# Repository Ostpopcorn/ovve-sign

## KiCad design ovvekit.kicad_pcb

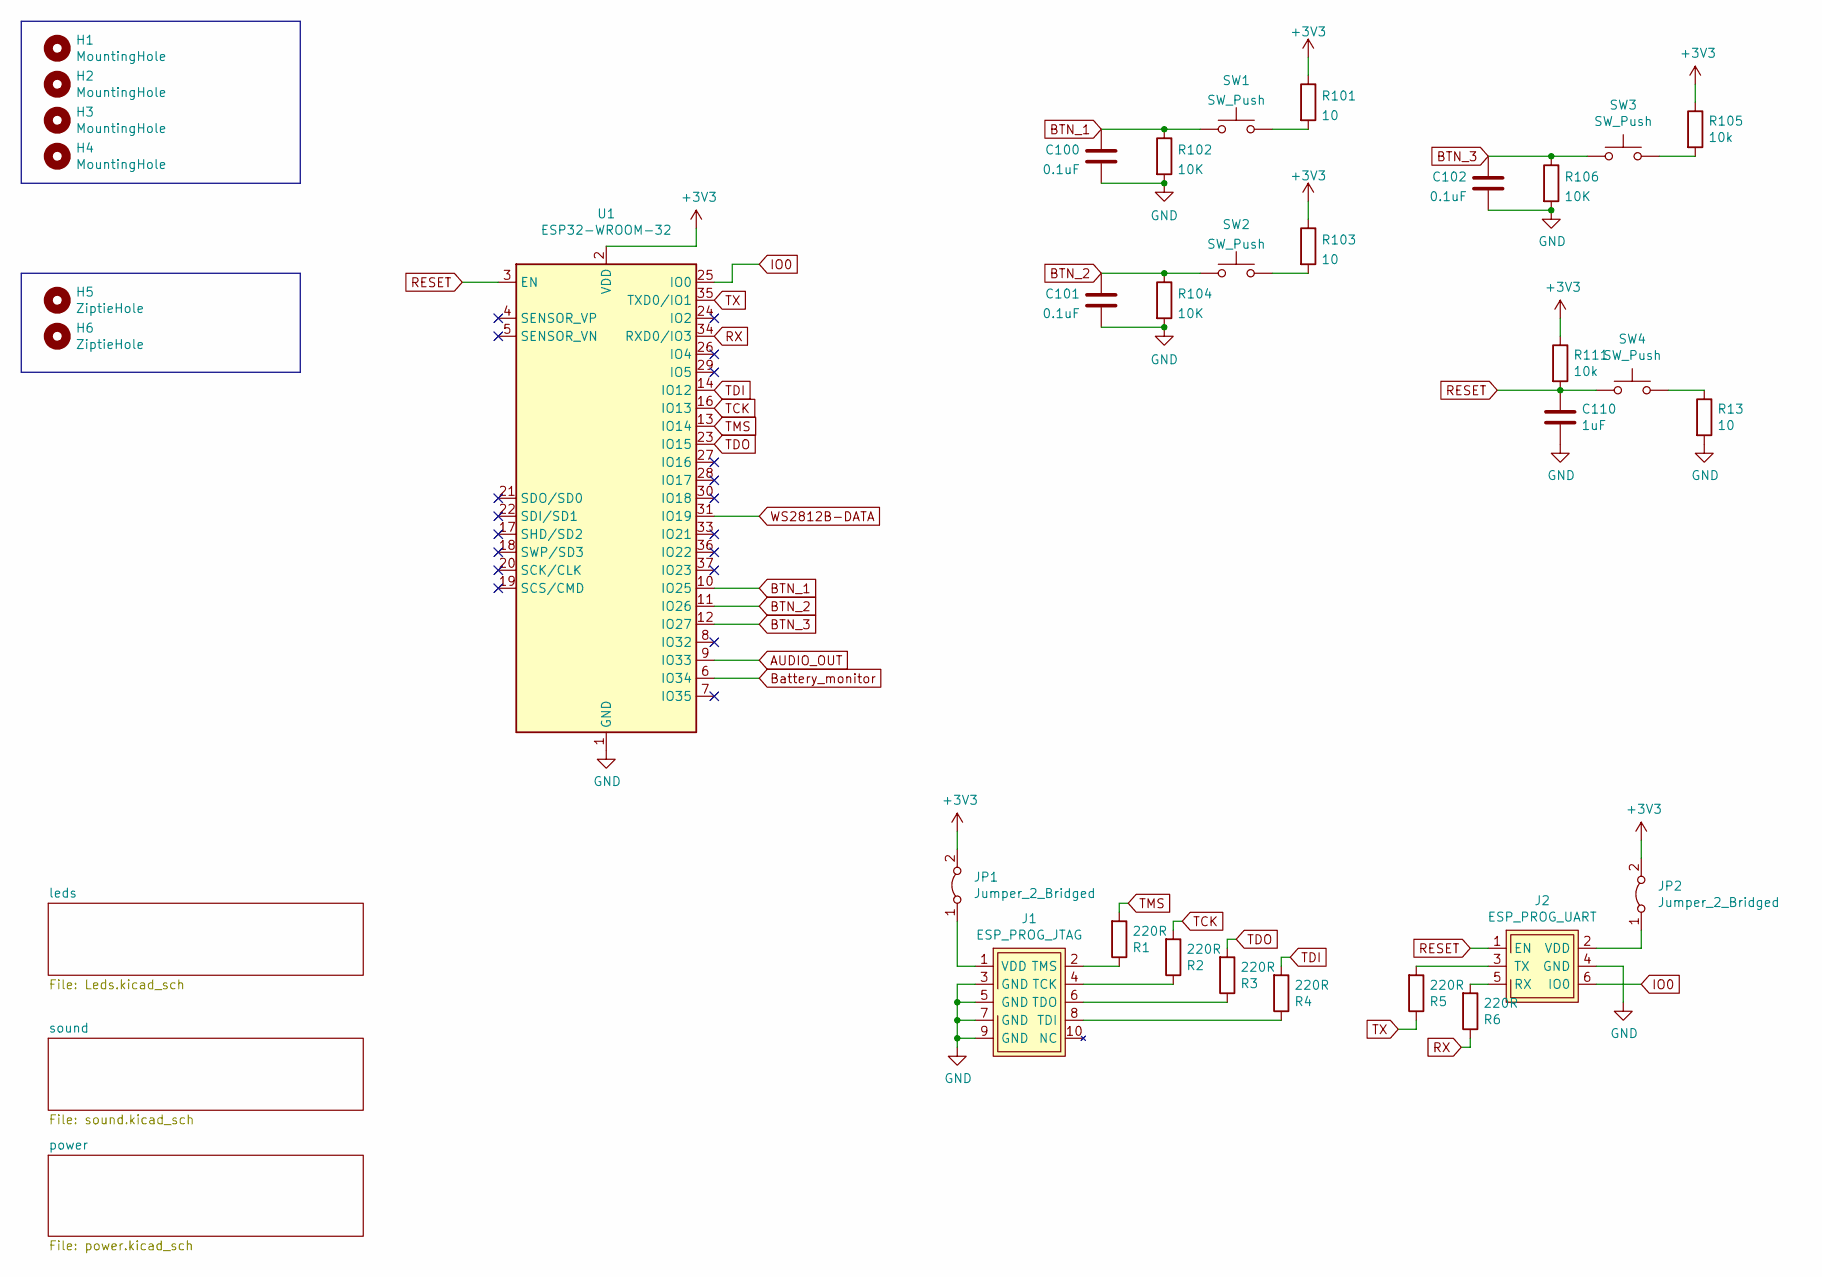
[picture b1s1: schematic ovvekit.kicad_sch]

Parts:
C100, C101, C102: 0.1uF; C_0603_1608Metric_Pad1.08x0.95mm_HandSolder
C110: 1uF; C_0603_1608Metric_Pad1.08x0.95mm_HandSolder
H1, H2, H3, H4: MountingHole; MountingHole_3.2mm_M3_ISO7380
H5, H6: ZiptieHole; MountingHole_2.7mm_M2.5_ISO7380
J1: ESP_PROG_JTAG; SMT_ESP_PROG_JTAG_1.27
J2: ESP_PROG_UART; SMT_ESP_PROG_PROG_1.27
JP1, JP2: Jumper_2_Bridged; SolderJumper-2_P1.3mm_Open_TrianglePad1.0x1.5mm
R1, R2, R3, R4, R5, R6: 220R; R_0603_1608Metric_Pad0.98x0.95mm_HandSolder
R13, R101, R103: 10; R_0603_1608Metric_Pad0.98x0.95mm_HandSolder
R102, R104, R106: 10K; R_0603_1608Metric_Pad0.98x0.95mm_HandSolder
R105, R111: 10k; R_0603_1608Metric_Pad0.98x0.95mm_HandSolder
SW1, SW2, SW3: SW_Push; SW_PUSH_6mm_H5mm
SW4: SW_Push; SW_SPST_TL3342
U1: ESP32-WROOM-32

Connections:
AUDIO_OUT: U1.9 (IO33); also elsewhere on the board
BTN_1: C100.1, R102.1, SW1.1, U1.10 (IO25)
BTN_2: C101.1, R104.1, SW2.1, U1.11 (IO26)
BTN_3: C102.1, R106.1, SW3.1, U1.12 (IO27)
Battery_monitor: U1.6 (IO34); also elsewhere on the board
GND: C100.2, C101.2, C102.2, C110.2, J1.3 (GND), J1.5 (GND), J1.7 (GND), J1.9 (GND), J2.4 (GND), R13.2, R102.2, R104.2, R106.2, U1.1 (GND), U1.15 (GND), U1.38 (GND), U1.39 (GND); also elsewhere on the board
IO0: J2.6 (IO0), U1.25 (IO0)
unnamed: J1.1 (VDD), JP1.1 (A)
unnamed: J1.2 (TMS), R1.1
unnamed: J1.4 (TCK), R2.1
unnamed: J1.6 (TDO), R3.1
unnamed: J1.8 (TDI), R4.1
unnamed: J2.2 (VDD), JP2.1 (A)
unnamed: J2.3 (TX), R5.2
unnamed: J2.5 (RX), R6.2
unnamed: R101.2, SW1.2
unnamed: R103.2, SW2.2
unnamed: R105.2, SW3.2
unnamed: R13.1, SW4.2
RESET: C110.1, J2.1 (EN), R111.2, SW4.1, U1.3 (EN)
RX: R6.1, U1.34 (RXD0/IO3)
TCK: R2.2, U1.16 (IO13)
TDI: R4.2, U1.14 (IO12)
TDO: R3.2, U1.23 (IO15)
TMS: R1.2, U1.13 (IO14)
TX: R5.1, U1.35 (TXD0/IO1)
WS2812B-DATA: U1.31 (IO19); also elsewhere on the board

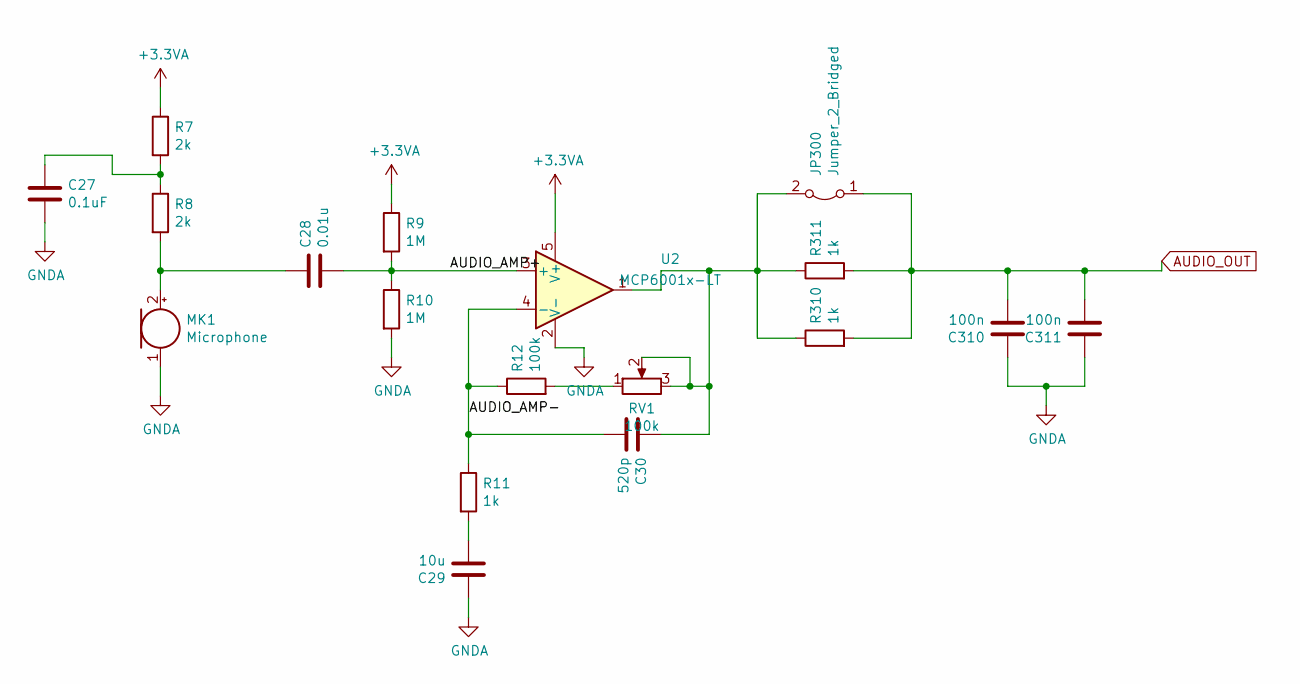
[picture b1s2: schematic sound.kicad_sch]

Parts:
C27: 0.1uF; C_0603_1608Metric_Pad1.08x0.95mm_HandSolder
C28: 0.01u; C_0603_1608Metric_Pad1.08x0.95mm_HandSolder
C29: 10u; C_0603_1608Metric_Pad1.08x0.95mm_HandSolder
C30: 520p; C_0603_1608Metric_Pad1.08x0.95mm_HandSolder
C310, C311: 100n; C_0603_1608Metric_Pad1.08x0.95mm_HandSolder
JP300: Jumper_2_Bridged; SolderJumper-2_P1.3mm_Open_TrianglePad1.0x1.5mm
MK1: Microphone; CMEJ062742P
R7, R8: 2k; R_0603_1608Metric_Pad0.98x0.95mm_HandSolder
R9, R10: 1M; R_0603_1608Metric_Pad0.98x0.95mm_HandSolder
R11, R310, R311: 1k; R_0603_1608Metric_Pad0.98x0.95mm_HandSolder
R12: 100k; R_0603_1608Metric_Pad0.98x0.95mm_HandSolder
RV1: 100k; Potentiometer_Bourns_3314S_Horizontal
U2: MCP6001x-LT; SOT-23-5

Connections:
+3.3VA: R7.1, R9.1, U2.5 (V+); also elsewhere on the board
/sound/AUDIO_AMP+: C28.2, R9.2, R10.1, U2.3 (+)
/sound/AUDIO_AMP-: C30.2, R11.1, R12.1, U2.4 (-)
AUDIO_OUT: C310.2, C311.2, JP300.1 (A), R310.2, R311.2; also elsewhere on the board
GNDA: C27.2, C29.1, C310.1, C311.1, MK1.1 (-), R10.2, U2.2 (V-); also elsewhere on the board
unnamed: C27.1, R7.2, R8.1
unnamed: C28.1, MK1.2 (+), R8.2
unnamed: C29.2, R11.2
unnamed: C30.1, JP300.2 (B), R310.1, R311.1, RV1.2, RV1.3, U2.1
unnamed: R12.2, RV1.1

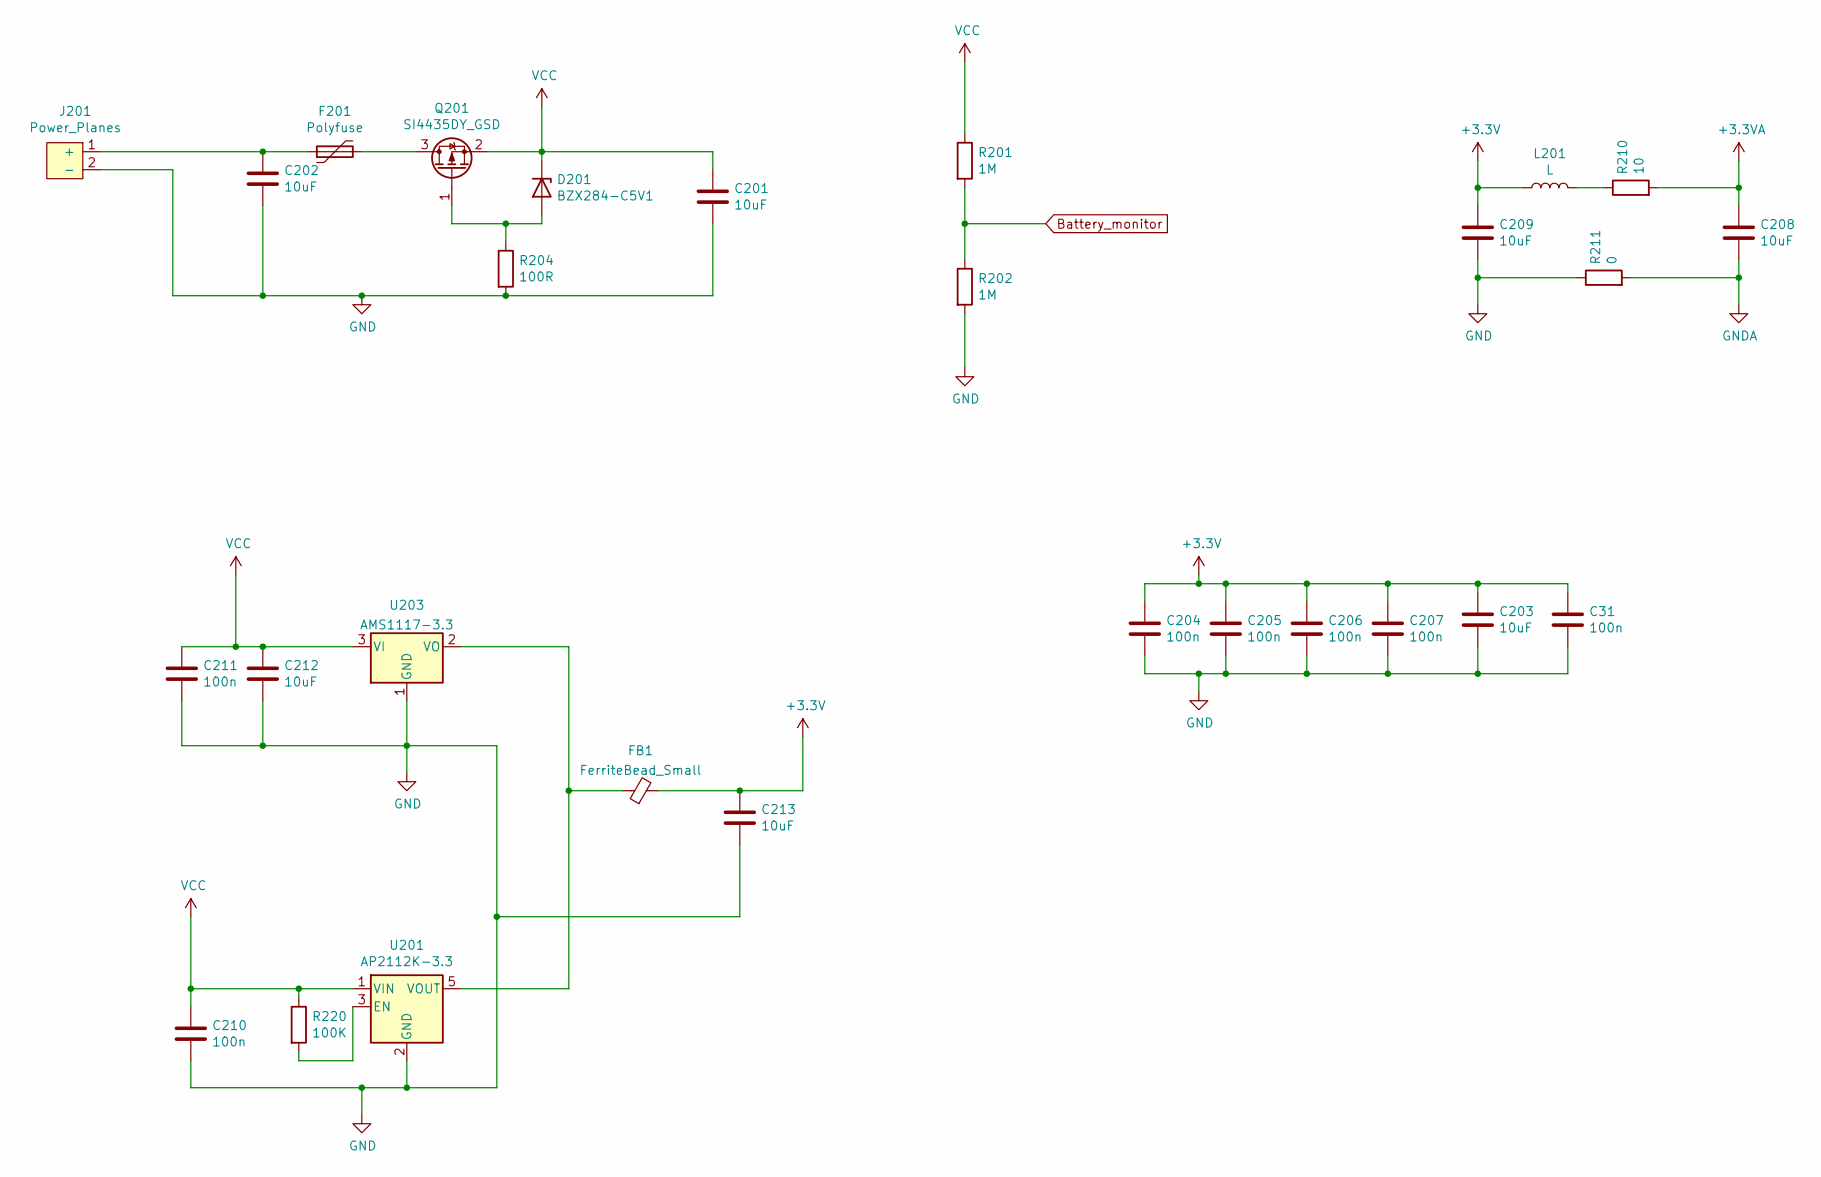
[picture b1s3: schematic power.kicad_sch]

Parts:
C31, C204, C205, C206, C207, C210, C211: 100n; C_0603_1608Metric_Pad1.08x0.95mm_HandSolder
C201, C202, C203, C208, C209, C212, C213: 10uF; C_1206_3216Metric_Pad1.33x1.80mm_HandSolder
D201: BZX284-C5V1; D_SOD-110
F201: Polyfuse; Fuse_1210_3225Metric_Pad1.42x2.65mm_HandSolder
FB1: FerriteBead_Small; C_1206_3216Metric_Pad1.33x1.80mm_HandSolder
J201: Power_Planes; Power_planes_3x6mm
L201: L; L_1206_3216Metric_Pad1.42x1.75mm_HandSolder
Q201: SI4435DY_GSD; SOIC-8_3.9x4.9mm_P1.27mm
R201, R202: 1M; R_0603_1608Metric_Pad0.98x0.95mm_HandSolder
R204: 100R; R_0603_1608Metric_Pad0.98x0.95mm_HandSolder
R210: 10; R_1206_3216Metric_Pad1.30x1.75mm_HandSolder
R211: 0; R_1206_3216Metric_Pad1.30x1.75mm_HandSolder
R220: 100K; R_0603_1608Metric_Pad0.98x0.95mm_HandSolder
U201: AP2112K-3.3; SOT-23-5
U203: AMS1117-3.3; SOT-223-3_TabPin2

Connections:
+3.3VA: C208.1, R210.2; also elsewhere on the board
Battery_monitor: R201.2, R202.1; also elsewhere on the board
GND: C31.2, C201.1, C202.1, C203.2, C204.2, C205.2, C206.2, C207.2, C209.2, C210.2, C211.2, C212.1, C213.2, J201.2 (-), R202.2, R204.2, R211.1, U201.2 (GND), U203.1 (GND); also elsewhere on the board
GNDA: C208.2, R211.2; also elsewhere on the board
unnamed: C202.2, F201.1, J201.1 (+)
unnamed: D201.2 (A), Q201.1 (G), R204.1
unnamed: F201.2, Q201.3 (D)
unnamed: FB1.1, U201.5 (VOUT), U203.2 (VO)
unnamed: L201.2, R210.1
unnamed: R220.2, U201.3 (EN)
VCC: C201.2, C210.1, C211.1, C212.2, D201.1 (K), Q201.2 (S), R201.1, R220.1, U201.1 (VIN), U203.3 (VI); also elsewhere on the board

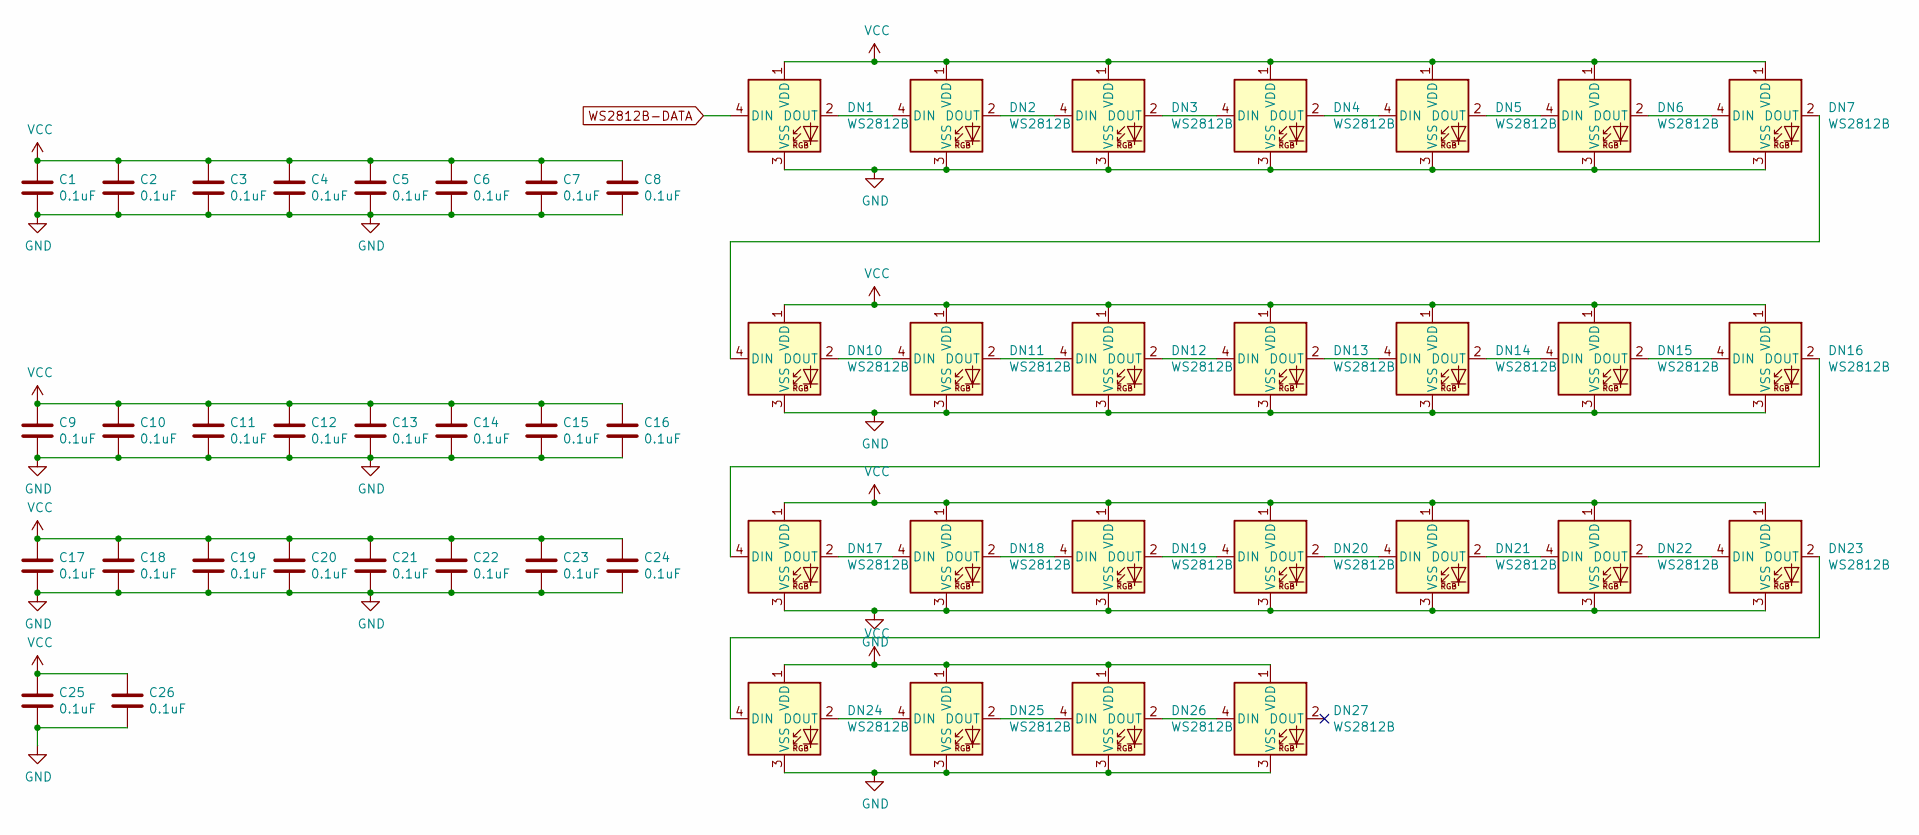
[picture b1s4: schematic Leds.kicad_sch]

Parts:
C1, C2, C3, C4, C5, C6, C7, C8, C9, C10, C11, C12, C13, C14, C15, C16, C17, C18, C19, C20, C21, C22, C23, C24, C25, C26: 0.1uF; C_0603_1608Metric_Pad1.08x0.95mm_HandSolder
DN1, DN2, DN3, DN4, DN5, DN6, DN7, DN10, DN11, DN12, DN13, DN14, DN15, DN16, DN17, DN18, DN19, DN20, DN21, DN22, DN23, DN24, DN25, DN26, DN27: WS2812B; LED_WS2812B_PLCC4_5.0x5.0mm_P3.2mm

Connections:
GND: C1.2, C2.2, C3.2, C4.2, C5.2, C6.2, C7.2, C8.2, C9.2, C10.2, C11.2, C12.2, C13.2, C14.2, C15.2, C16.2, C17.2, C18.2, C19.2, C20.2, C21.2, C22.2, C23.2, C24.2, C25.2, C26.2, DN1.3 (VSS), DN2.3 (VSS), DN3.3 (VSS), DN4.3 (VSS), DN5.3 (VSS), DN6.3 (VSS), DN7.3 (VSS), DN10.3 (VSS), DN11.3 (VSS), DN12.3 (VSS), DN13.3 (VSS), DN14.3 (VSS), DN15.3 (VSS), DN16.3 (VSS), DN17.3 (VSS), DN18.3 (VSS), DN19.3 (VSS), DN20.3 (VSS), DN21.3 (VSS), DN22.3 (VSS), DN23.3 (VSS), DN24.3 (VSS), DN25.3 (VSS), DN26.3 (VSS), DN27.3 (VSS); also elsewhere on the board
unnamed: DN1.2 (DOUT), DN2.4 (DIN)
unnamed: DN2.2 (DOUT), DN3.4 (DIN)
unnamed: DN3.2 (DOUT), DN4.4 (DIN)
unnamed: DN4.2 (DOUT), DN5.4 (DIN)
unnamed: DN5.2 (DOUT), DN6.4 (DIN)
unnamed: DN6.2 (DOUT), DN7.4 (DIN)
unnamed: DN10.2 (DOUT), DN11.4 (DIN)
unnamed: DN7.2 (DOUT), DN10.4 (DIN)
unnamed: DN11.2 (DOUT), DN12.4 (DIN)
unnamed: DN12.2 (DOUT), DN13.4 (DIN)
unnamed: DN13.2 (DOUT), DN14.4 (DIN)
unnamed: DN14.2 (DOUT), DN15.4 (DIN)
unnamed: DN15.2 (DOUT), DN16.4 (DIN)
unnamed: DN16.2 (DOUT), DN17.4 (DIN)
unnamed: DN17.2 (DOUT), DN18.4 (DIN)
unnamed: DN18.2 (DOUT), DN19.4 (DIN)
unnamed: DN19.2 (DOUT), DN20.4 (DIN)
unnamed: DN20.2 (DOUT), DN21.4 (DIN)
unnamed: DN21.2 (DOUT), DN22.4 (DIN)
unnamed: DN22.2 (DOUT), DN23.4 (DIN)
unnamed: DN23.2 (DOUT), DN24.4 (DIN)
unnamed: DN24.2 (DOUT), DN25.4 (DIN)
unnamed: DN25.2 (DOUT), DN26.4 (DIN)
unnamed: DN26.2 (DOUT), DN27.4 (DIN)
VCC: C1.1, C2.1, C3.1, C4.1, C5.1, C6.1, C7.1, C8.1, C9.1, C10.1, C11.1, C12.1, C13.1, C14.1, C15.1, C16.1, C17.1, C18.1, C19.1, C20.1, C21.1, C22.1, C23.1, C24.1, C25.1, C26.1, DN1.1 (VDD), DN2.1 (VDD), DN3.1 (VDD), DN4.1 (VDD), DN5.1 (VDD), DN6.1 (VDD), DN7.1 (VDD), DN10.1 (VDD), DN11.1 (VDD), DN12.1 (VDD), DN13.1 (VDD), DN14.1 (VDD), DN15.1 (VDD), DN16.1 (VDD), DN17.1 (VDD), DN18.1 (VDD), DN19.1 (VDD), DN20.1 (VDD), DN21.1 (VDD), DN22.1 (VDD), DN23.1 (VDD), DN24.1 (VDD), DN25.1 (VDD), DN26.1 (VDD), DN27.1 (VDD); also elsewhere on the board
WS2812B-DATA: DN1.4 (DIN); also elsewhere on the board

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
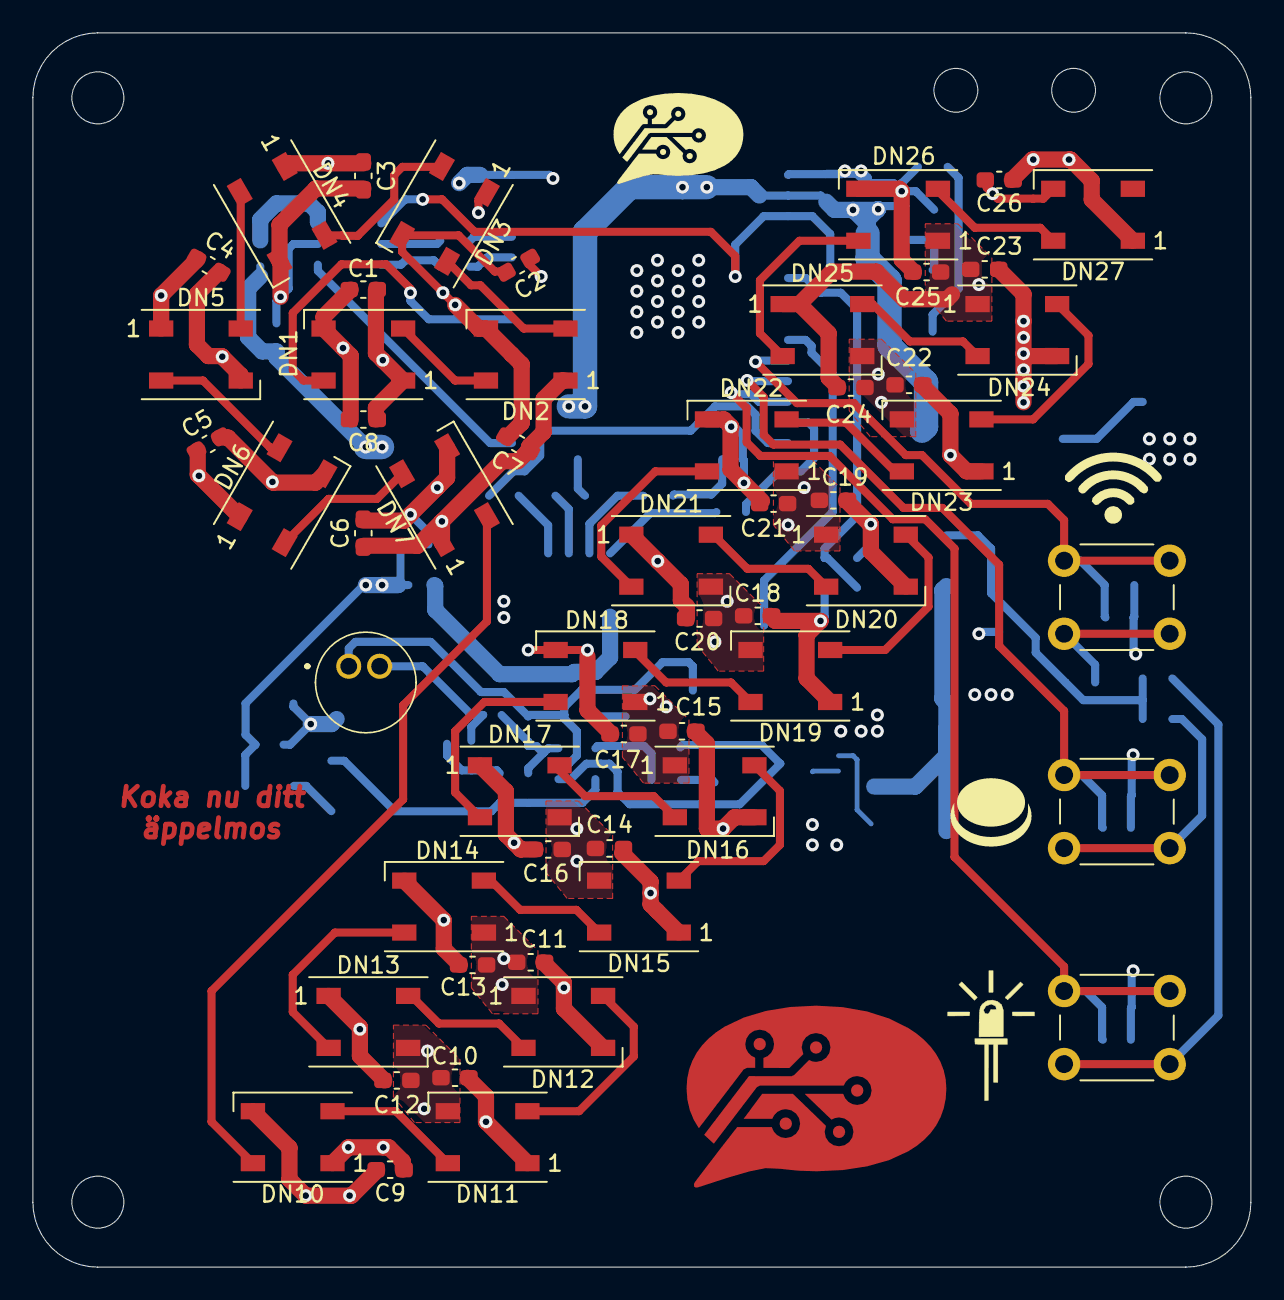
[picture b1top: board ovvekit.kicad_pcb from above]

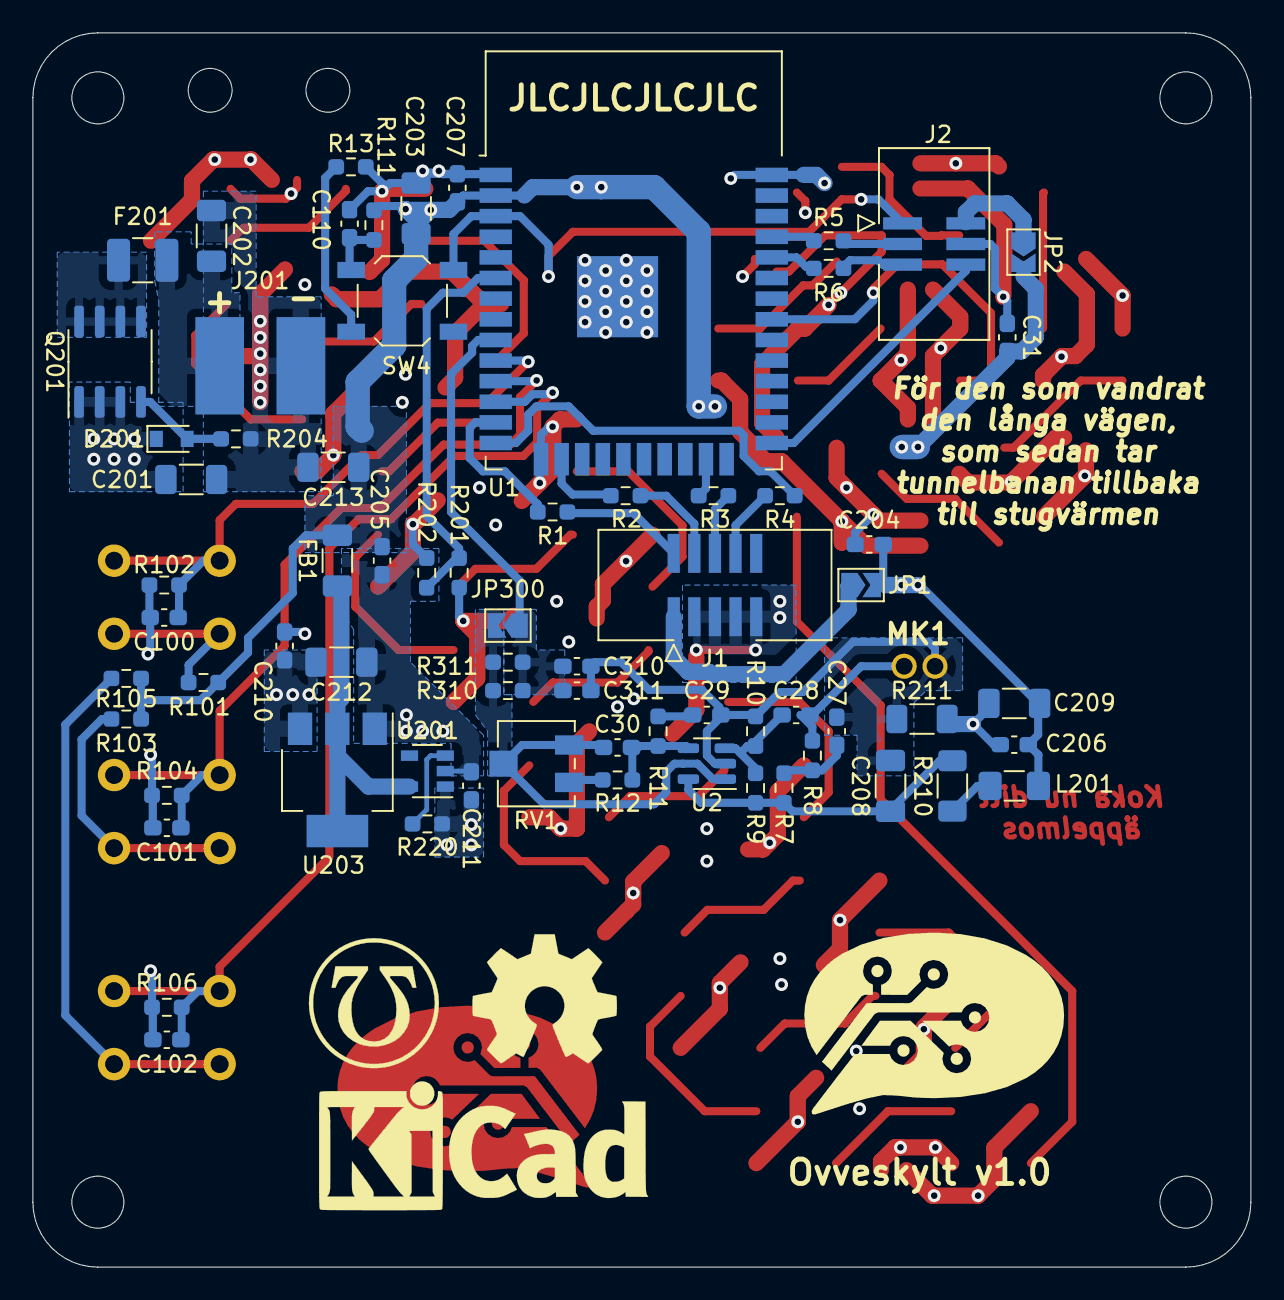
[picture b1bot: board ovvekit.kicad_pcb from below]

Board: 4 copper layers, 75.0 x 76.0 mm, 137 parts (71 on the bottom side), 68 nets.

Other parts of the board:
button_5mm_SilkScreen: G***; button_5mm_SilkScreen
led_12mm_SilkScreen: G***; led_8mm_SilkScreen
svg2mod: G***; OST-Logo_40mm_Copper
svg2mod#2: G***; bubbla_8mm_SilkScreen
svg2mod#3: G001; admittansen_8mm_SilkScreen
svg2mod#4: G***; bubbla_16mm_SilkScreen
wifi_5mm_SilkScreen: G***; wifi_6mm_SilkScreen

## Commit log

2021-09-09 Added all kicad files, except for submodules.
2021-09-09 Addded git submodules.
2021-09-09 Added special parts lib. Containing the connector for power.
2021-09-09 Changed board size to Y is centered.
2021-09-11 Updated .gitmodules so the syntax is correct.
2021-09-11 Changed so mic is in local library.
2021-09-11 Still trying to separate out Samacsys lib to make it standalone.
2021-09-11 Now amplifier is in local lib, hopefully.
2021-09-11 Now all footprint are updated to. SamacSys is no longer a dependency of this project.
2021-09-14 Added a LDO, maybe not the final one but there is one on the PCB now. Added a voltage divider for measureing battery voltage.
2021-09-15 Fixed merge conflic in cache file.
2021-09-27 Added some 1206 caps to be large stabilizing capacitors. Added a rank 1 RC filter to audio out, with a bypass solderbridge if wanted.
2021-10-05 Added a 9-dof IMU, however it cant be sourced because of chips. But it is a start.
2021-10-05 Added some primitive filter for 3V3A and GNDA. Added the IMU to the board.
2021-10-06 Added more filtering. Placed bypass caps near esp32 power intake.
2022-01-19 Updated to kicad 6. Added AMS1117 regulator. Did more layout work in power section.
2022-01-19 Updated PCB after DRC. Updated Connector lib.
2022-01-19 Conected up the last nets.
2022-01-19 Added more logos!
2022-01-21 Updated symbolOST lib with new symbols.
2022-01-21 Updated .gitignore to exclude gbr files and folders.
2022-01-21 Updated SymbolOST, again.
2022-01-27 Updated all but polyfuse and ferride bead to correct footprints.
2022-01-27 Updated SymbolOST lib
2022-01-27 Merged changes from both computers. Moved some components. Next i redoing power section again...
2022-01-29 Updated power section. Updated all possible footprints to be "hand solder" version. Updated Symbol lib.
2022-01-30 Update to correct OP-amp. This is the version sent to production.
2022-01-30 ... Forgot to connect the data line to esp32... It's done now.
2022-02-03 Fixed version commited to JLC.
2022-02-21 Fixed known errors. * Reset curcuit, know is pull high with button tieing it low * OP-amp now uses correct, larger, footprint.
